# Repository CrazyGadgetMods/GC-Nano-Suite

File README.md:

# GC Nano

This repo contains the suite of custom PCBs required to build the GC Nano v1 / v1.1, with the exception of the [PSU-Plus](https://github.com/CrazyGadgetMods/PSU-Plus). All 3D model files (as well as a more formal release post) can be found in the [GC Nano - The Worlds Smallest Gamecube](https://bitbuilt.net/forums/index.php?threads/gc-nano-the-worlds-smallest-gamecube.5697/) thread on the BitBuilt Forums.

## Top Board
- USB type C port with 5.1k ohm resistors on each of the CC lines to enable any Power Delivery (PD) compliant charger to output 5V @ 3A.
- MAX16054 Push-On / Push-Off IC paired with a PFET to turn the system on and off with a single tact switch
- GL823K Micro SD to USB converter IC.
- USB MUX - when the system is off, the USB data lines connect to the USB-C port, allowing file transfer without having to open up the case; when the system is on, the USB data lines go to two pads which get soldered to the Wii.
- Sync and Reset buttons to be soldered to the bluetooth module / Wii.

## Controller Board
- Solders right to the TRRS jacks, eliminating the need for any daisy-chain hand-wiring between the ports.
- Three power pads are wired to the complimentary set on the top board for clean assembly.
- Data lines get wired to the Wii
- Incorporates pull-up resistors for the data lines, as the original resistor array is cut off for the OMEGA trim.

## HDMI-FFC
- Allows us to mount the HDMI port to the back handle, as well as interface it with the AVE-HDMI via an FFC cable.

## Credits
- [Wesk](https://bitbuilt.net/forums/index.php?members/wesk.1486/): Inviting me to collaborate on the GC Nano project, creating the GC Micro
- [Madmorda](https://bitbuilt.net/forums/index.php?members/madmorda.554/): Creating the original [World's Smallest Gamecube](https://www.youtube.com/watch?v=_BxwS_uTKt4)
- [YveltalGriffin](https://github.com/mackieks): Advice while designing the Top Board / PSU-Plus
- [BitBuilt](https://bitbuilt.net/): Being the best modding community out there!

## License
Solderpad Hardware License v2.1

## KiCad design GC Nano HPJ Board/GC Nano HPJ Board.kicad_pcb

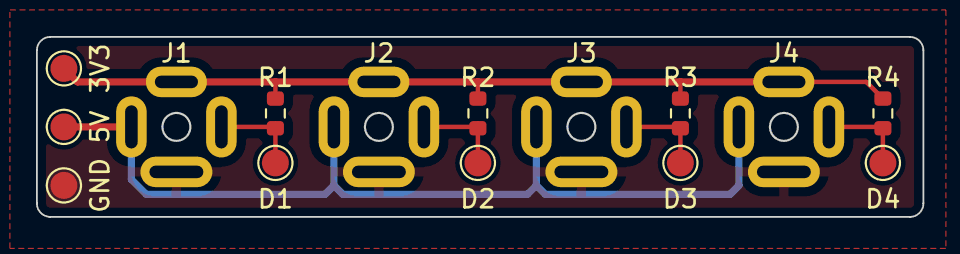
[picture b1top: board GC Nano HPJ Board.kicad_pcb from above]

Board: 2 copper layers, 49.2 x 10.0 mm, 15 parts (0 on the bottom side), 7 nets.

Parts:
3V3: 3V3; TestPoint_Pad_D1.5mm
5V: 5V; TestPoint_Pad_D1.5mm
D1, D2, D3, D4: GCD; TestPoint_Pad_D1.5mm
GND: GND; TestPoint_Pad_D1.5mm
J1, J2, J3, J4: ASJ-165-M-G-HDW-1
R1, R2, R3, R4: 10k; R_0603_1608Metric

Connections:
+3V3: 3V3.1, J1.3 (Ring_1), J2.3 (Ring_1), J3.3 (Ring_1), J4.3 (Ring_1), R1.2, R2.2, R3.2, R4.2
+5V: 5V.1, J1.2 (Tip), J2.2 (Tip), J3.2 (Tip), J4.2 (Tip)
GND: GND.1, J1.1 (Sleeve), J2.1 (Sleeve), J3.1 (Sleeve), J4.1 (Sleeve)
unnamed: D1.1, J1.4 (Ring_2), R1.1
unnamed: D2.1, J2.4 (Ring_2), R2.1
unnamed: D3.1, J3.4 (Ring_2), R3.1
unnamed: D4.1, J4.4 (Ring_2), R4.1

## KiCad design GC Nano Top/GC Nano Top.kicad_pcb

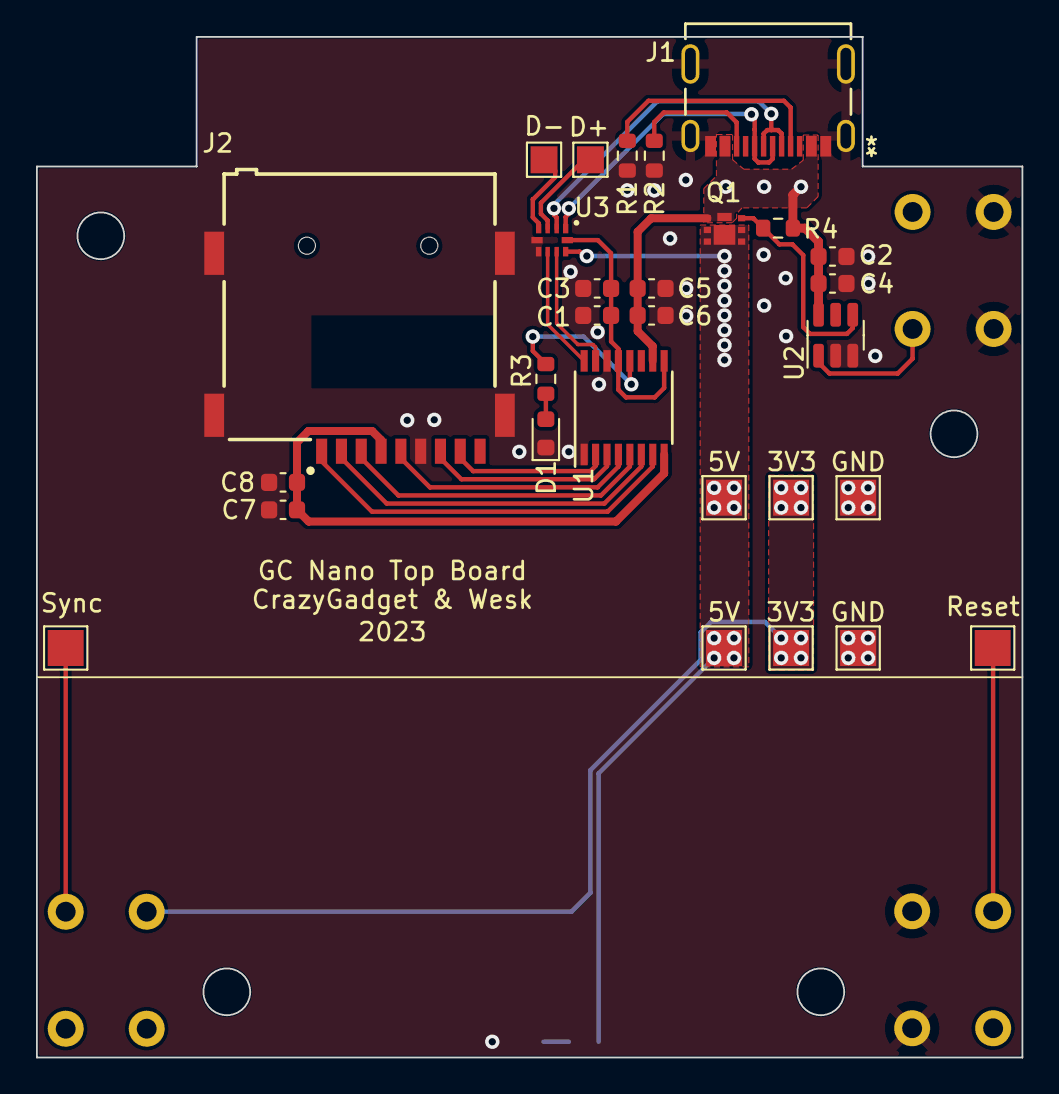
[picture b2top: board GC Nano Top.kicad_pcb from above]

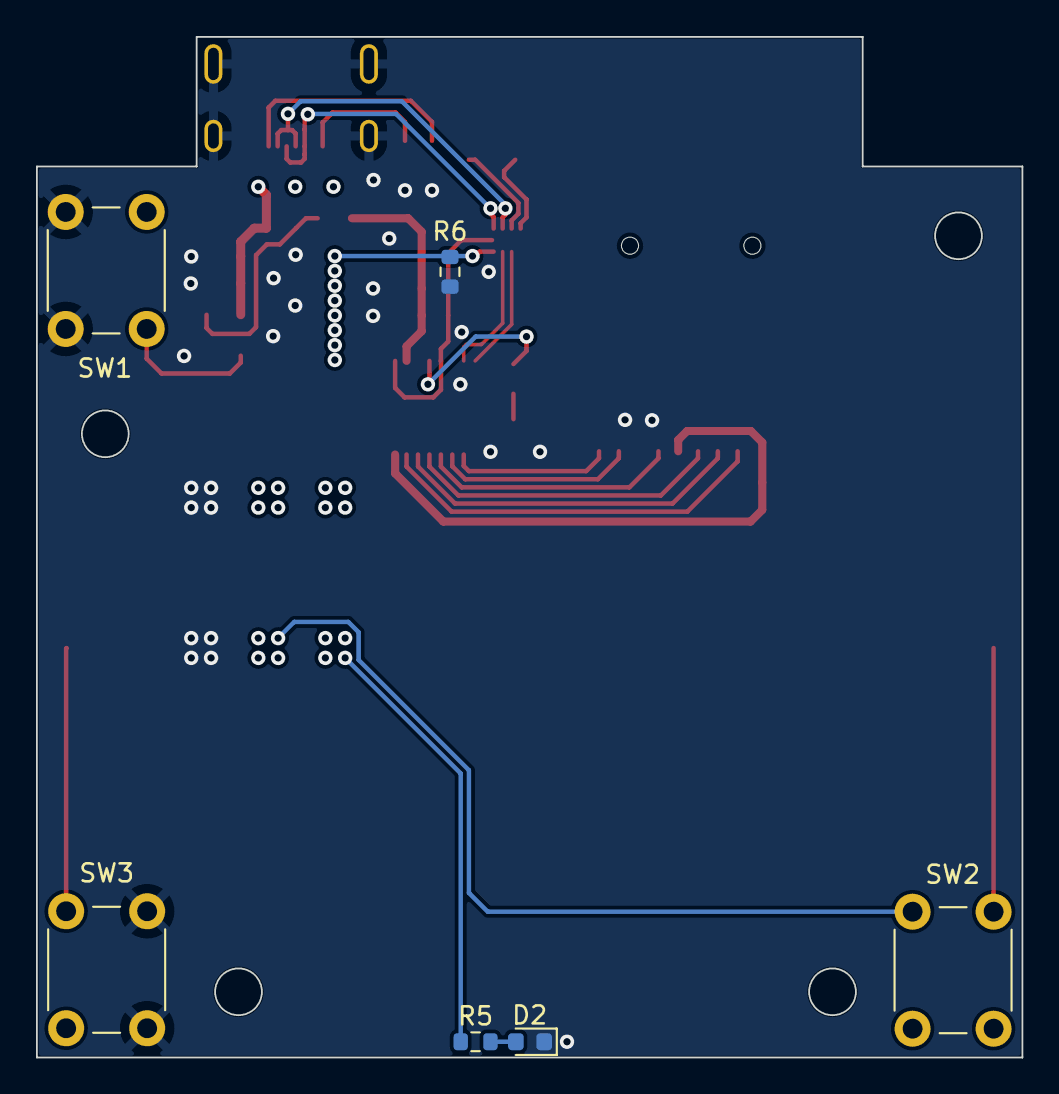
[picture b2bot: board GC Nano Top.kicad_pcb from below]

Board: 2 copper layers, 54.8 x 56.7 mm, 35 parts (6 on the bottom side), 27 nets.

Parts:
3V3, 3V3#2: 3V3; TestPoint_Pad_2.0x2.0mm
5V: 5V; TestPoint_Pad_2.0x2.0mm
5V#2: 5V_SW; TestPoint_Pad_2.0x2.0mm
C1, C2, C5, C7: 1u; C_0603_1608Metric
C3, C4, C6, C8: 0.1u; C_0603_1608Metric
D1, D2: LED; LED_0603_1608Metric
D+: D+Wii; TestPoint_Pad_1.5x1.5mm
D-: D-Wii; TestPoint_Pad_1.5x1.5mm
GND: GND; TestPoint_Pad_2.0x2.0mm
GND#2: GND; TestPoint_Pad_2.0x2.0mm
J1: USB_C_Receptacle_USB2.0; 2171790001_MOL
J2: MEM2075-00-140-01-A; GCT_MEM2075-00-140-01-A
Q1: PMPB17EP
R1, R2: 5.1k; R_0603_1608Metric
R3, R5: 330; R_0603_1608Metric
R4: 100k; R_0603_1608Metric
R6: R_0603_1608Metric
Reset: Reset; TestPoint_Pad_2.0x2.0mm
SW1, SW2, SW3: SW_Push; SW_PUSH_6mm
Sync: Sync; TestPoint_Pad_2.0x2.0mm
U1: GL823K-HCY04; SSOP-16_3.9x4.9mm_P0.635mm
U2: MAX16054; TSOT-23-6
U3: PI3USB221AZUAEX; PI3USB221A

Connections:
3V3: 3V3.1, 3V3#2.1, SW2.1
3V3_MUX: C1.1, C3.1, U1.9 (VDD), U1.13 (VDDA), U3.10 (VDD)
5V_IN: C2.1, C4.1, C5.1, C6.1, J1.A4/B9, J1.B4/A9, Q1.4 (S), Q1.8 (S), R4.2, U1.10 (5V), U2.6 (VCC)
5V_SW: 5V.1, 5V#2.1, Q1.1 (D), Q1.2 (D), Q1.5 (D), Q1.6 (D), Q1.7 (D), R5.1, R6.2, U3.9 (S)
CLK: J2.P5 (CLK), U1.4 (CLK)
CMD: J2.P3 (CMD), U1.5 (CMD)
D0: J2.P7 (DAT0), U1.3 (D0)
D1: J2.P8 (DAT1), U1.2 (D1)
D2: J2.P1 (DAT2), U1.7 (D2)
D3: J2.P2 (CD/DAT3), U1.6 (D3)
D+: U1.15 (DP), U3.8 (D+)
D+C: J1.A6 (D+), J1.B6 (D+), U3.1 (1D+)
D-: U1.16 (DM), U3.7 (D-)
D-C: J1.A7 (D-), J1.B7 (D-), U3.2 (1D-)
GND: C1.2, C2.2, C3.2, C4.2, C5.2, C6.2, C7.2, C8.2, D1.1 (K), D2.1 (K), GND.1, GND#2.1, J1.13, J1.14, J1.15, J1.16, J1.A1/B12, J1.B1/A12, J2.P6 (VSS), J2.SH1 (SHIELD), J2.SH2 (SHIELD), J2.SH3 (SHIELD), J2.SH4 (SHIELD), R1.2, R2.2, R6.1, SW1.1, SW3.1, U1.1 (VSS), U1.14 (VSS), U2.2 (GND), U2.3 (CLEAR), U3.5 (GND), U3.6 (~{OE)
unnamed: D1.2 (A), R3.2
unnamed: D2.2 (A), R5.2
unnamed: J1.A5 (CC1), R1.1
unnamed: J1.B5 (CC2), R2.1
unnamed: R3.1, U1.12 (LED)
unnamed: SW1.2, U2.1 (IN)
unnamed: SW2.2, Sync.1
unnamed: Reset.1, SW3.2
unnamed: D+.1, U3.3 (2D+)
unnamed: D-.1, U3.4 (2D-)
SD_PMOS: C7.1, C8.1, J2.P4 (VDD), U1.8 (PMOS)
~OUT: Q1.3 (G), R4.1, U2.4 (~OUT)

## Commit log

2024-05-13 init
